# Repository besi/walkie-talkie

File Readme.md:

Walkie Talkie
=============

## Acknowledgements

- Thanks to Chris for creating his version of the [ESP32 walkie talkie](https://easyeda.com/chris_9044/esp32-walkie-talkie)

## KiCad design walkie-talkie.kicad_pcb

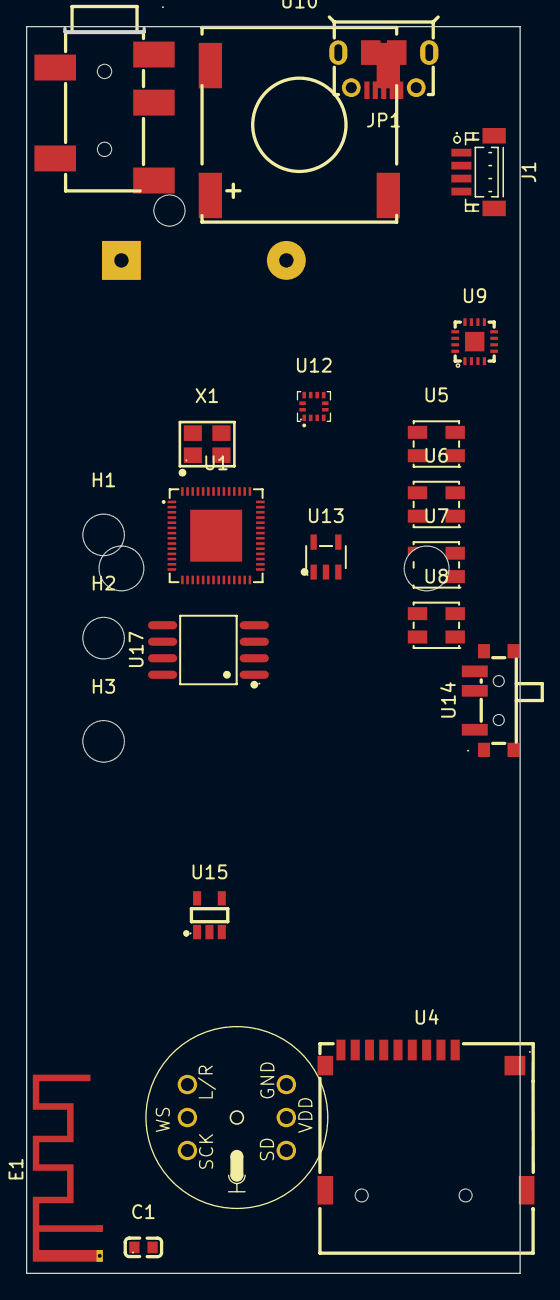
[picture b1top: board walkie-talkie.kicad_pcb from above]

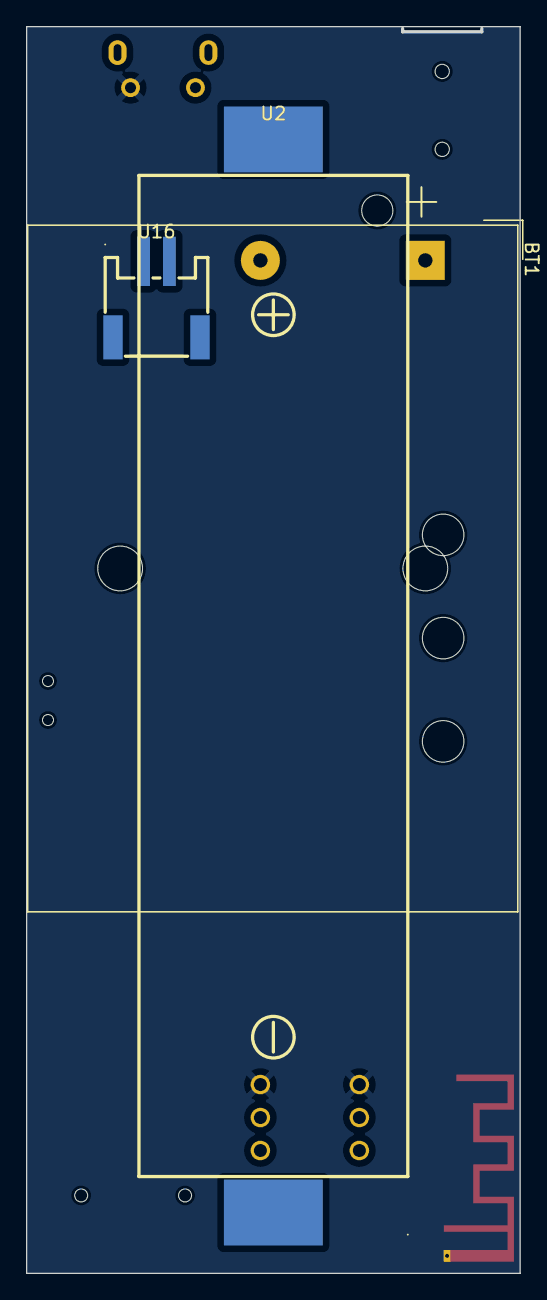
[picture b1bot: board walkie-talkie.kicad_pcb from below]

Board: 2 copper layers, 37.8 x 95.8 mm, 26 parts (3 on the bottom side), 8 nets, no tracks yet.

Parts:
BT1: Battery_Cell; BatteryHolder_Keystone_2479_3xAAA
C1: 5.6p; C0603
E1: Antenna_Trace; Texas_SWRA117D_2.4GHz_Right
H1, H2, H3: MountingHole; MountingHole_3.2mm_M3
J1: I2C; CONN-SMD_BM04B-SRSS-TB
JP1: USB_B_Micro; MICRO-USB-SMD_1050171001
U1: ESP32-S3(R8); QFN-56_L7.0-W7.0-P0.40-TL-EP4.0
U2: BH-18650-B1BA002; BATTERY-SMD_18650-1S-L77.1-W20.7-1
U3: mems-mic; mems-mic-round
U4: TF-115; TF-SMD_TF-115
U5, U6, U7, U8: SK6812MINI-HS; LED-SMD_4P-L3.5-W3.5-BR_SK6812MINI-HS
U9: MAX98357AETE+T; TQFN-16_L3.0-W3.0-P0.50-BL-EP1.5
U10: FS-1540; BUZ-SMD_5P-L15.0-W15.0-P13.7-BL
U11: PJ-327A_5JJ; AUDIO-SMD_PJ-327A5JJ
U12: LIS2DH12TR; LGA-12_L2.0-W2.0-P0.50-BL
U13: MCP73831T-2ACI_OT; SOT-23-5_L3.0-W1.7-P0.95-LS2.8-BL
U14: ON; SW-SMD_MK-12C02-G020
U15: AP2112K-3_3TRG1; SOT-25-5_L2.9-W1.6-P0.95-LS2.8-BL
U16: +; CONN-SMD_P2.00_S2B-PH-SM4-TB-LF-SN
U17: W25Q128JVSIQTR; SOIC-8_L5.3-W5.3-P1.27-LS8.0-BL
X1: X322540MPB4SI; OSC-SMD_4P-L3.2-W2.5-BL_SIT8008BI

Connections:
+3V3: J1.2, U3.1 (3V), U5.3 (VDD), U6.3 (VDD), U7.3 (VDD), U8.3 (VDD), U17.8 (VCC)
ANT: C1.2, E1.1 (A)
GND: E1.2 (Shield), J1.0, J1.1, JP1.5 (GND), JP1.6 (Shield), U3.2 (GND), U3.6 (SEL), U5.1 (GND), U6.1 (GND), U7.1 (GND), U8.1 (GND), U17.4 (GND)
unnamed: U5.4 (DOUT), U6.2 (DIN)
unnamed: U6.4 (DOUT), U7.2 (DIN)
unnamed: U7.4 (DOUT), U8.2 (DIN)
USB_N: JP1.2 (D-), U1.25 (GPIO19)
USB_P: JP1.3 (D+), U1.26 (GPIO20)

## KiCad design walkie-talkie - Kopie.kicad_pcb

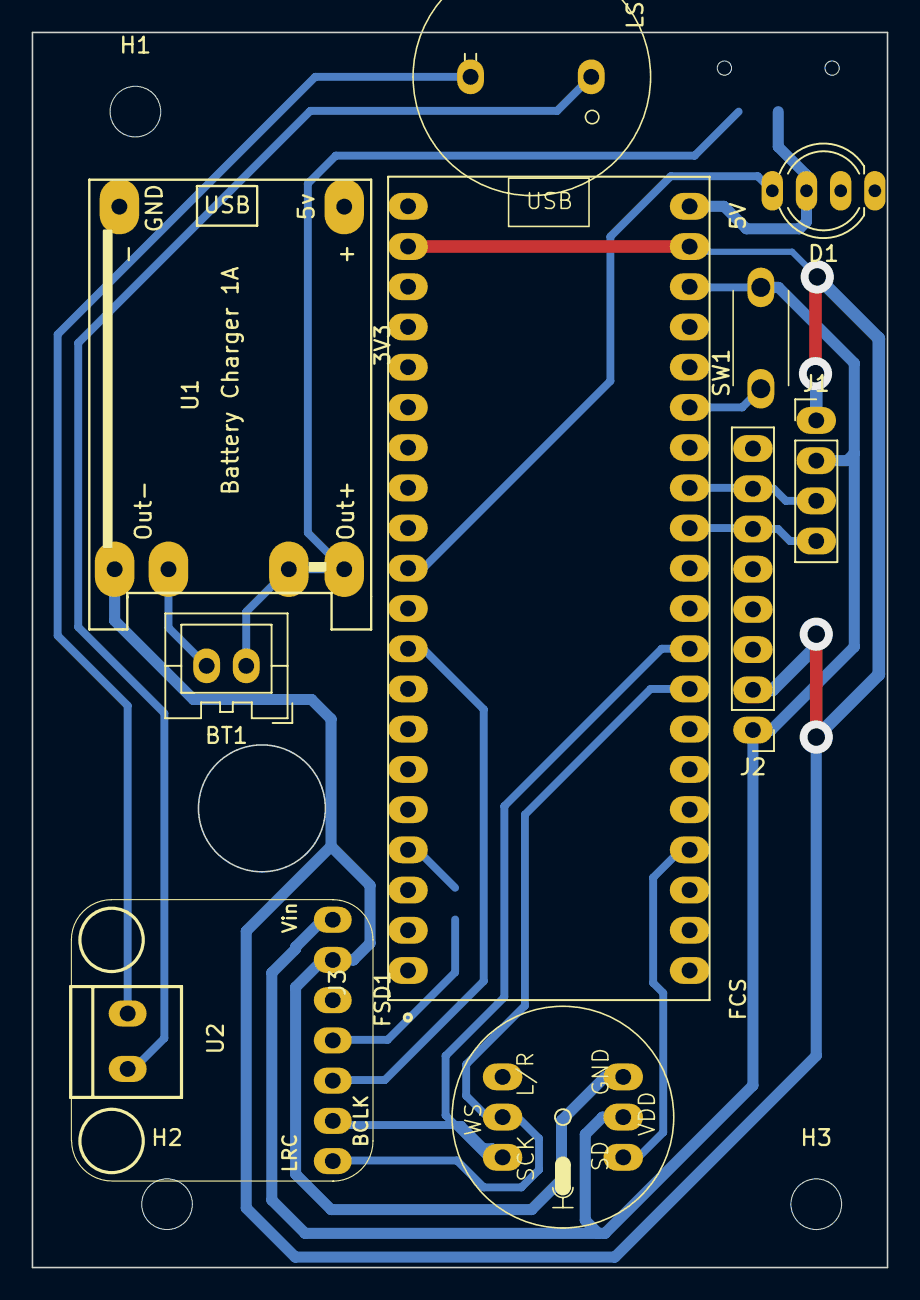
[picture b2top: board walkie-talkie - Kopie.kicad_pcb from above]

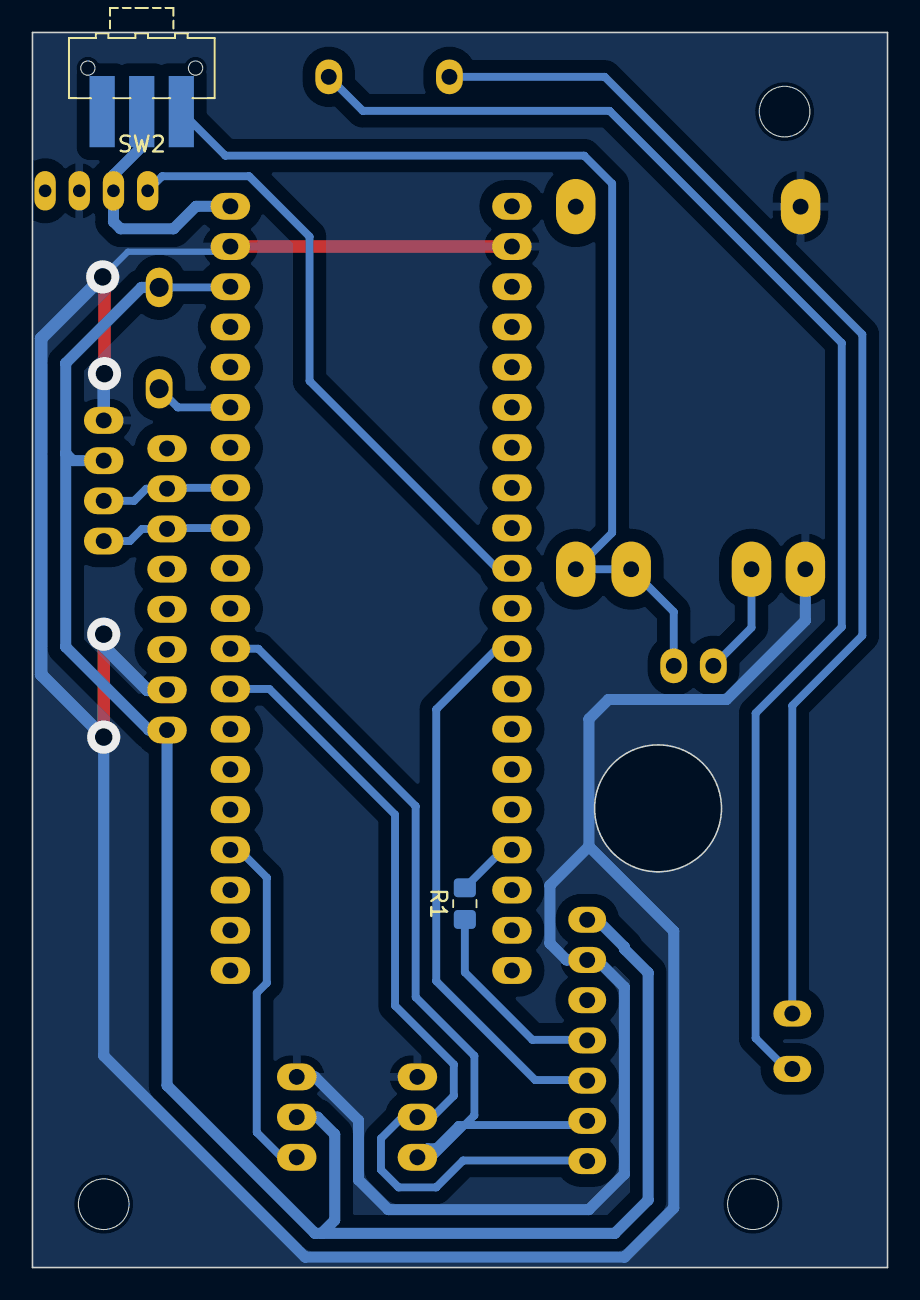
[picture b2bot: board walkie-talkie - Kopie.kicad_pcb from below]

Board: 2 copper layers, 54.0 x 78.0 mm, 15 parts (2 on the bottom side), 17 nets.

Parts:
BT1: Battery_Cell; JST_XA_B02B-XASK-1_1x02_P2.50mm_Vertical
D1: NeoPixel_THT; LED_D5.0mm-4_RGB_Wide_Pins
H1, H2, H3: MountingHole; MountingHole_3.2mm_M3
J1: I2C; PinHeader_1x04_P2.54mm_Vertical
J2: Conn_01x08; PinHeader_1x08_P2.54mm_Vertical
J3: esp32-pico-kit
LS1: Speaker; PinSocket_1x04_P2.54mm_Horizontal
R1: 100k; R_0805_2012Metric_Pad1.20x1.40mm_HandSolder
SW1: Transmit; pts636
SW2: POWER; SW_SPDT_CK-JS102011SAQN
U1: WARNING: Switch off when Plugging in Power on the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; tp4056
U2: adafruit-MAX98357
U3: mems-mic; mems-mic-round

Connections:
+3V3: J1.2, J2.1, J3.J3_18 (VDD33_2), SW1.2, U2.1 (Vin), U3.1 (3V)
+5V: D1.3 (VDD), J3.J3_20 (EXT_5V), SW2.2 (B)
GND: D1.2 (GND), J1.1, J2.2, J3.J2_19 (GND_1), J3.J3_19 (GND_2), U1.2 (IN-), U1.6 (O-), U2.2 (GND), U3.2 (GND), U3.6 (SEL)
I2C_SCL: J1.4, J2.6, J3.J3_12 (IO12)
I2C_SDA: J1.3, J2.7, J3.J3_13 (IO13)
I2S_AMP_DATA: J3.J2_9 (IO5), U2.5 (DIN)
I2S_AMP_GAIN: J3.J2_4 (IO21), R1.2
I2S_BCLK: J3.J3_9 (IO33), U2.6 (BCLK), U3.3 (BCLK)
I2S_MIC_DATA: J3.J3_4 (SENSOR_VP/IO36), U3.4 (DOUT)
I2S_RLCLK: J3.J3_8 (IO32), U2.7 (LRC), U3.5 (LRCLK)
unnamed: BT1.1 (+), SW2.1 (A), U1.3 (B+), U1.5 (O+)
unnamed: BT1.2 (-), U1.4 (B-)
unnamed: D1.4 (DIN), J3.J2_11 (IO9)
unnamed: J3.J3_15 (IO2), SW1.1
unnamed: R1.1, U2.4 (GAIN)
unnamed: LS1.2, U2.9 (OUTN)
unnamed: LS1.1, U2.8 (OUTP)

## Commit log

2024-03-26 esp32 poe, audio and acc tests
2024-04-02 Add dependencies
2024-04-03 Routing of pico pcb
2024-04-03 Add mounting holes
2024-04-04 Add CVS speaker
2024-04-04 Lolin32-Lite PCB
2024-04-04 Neatify schematics
2024-04-04 Plotting updates
2024-04-04 .gitignore
2024-04-12 walkie talkie micropython (low quality version, try tuning the sample rate)
2024-04-15 Wire the neopixel
2024-04-17 Add components for new PCB
2025-01-08 Add ackknowledgements to Readme
2025-01-08 Add new symbols
